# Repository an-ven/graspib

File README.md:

# GrasPiB
GPIB interface board for Raspberry Pi, designed to work with [linux-gpib](https://linux-gpib.sourceforge.io/) gpio bitbang driver. Extra features include: RS232 serial interface, voltage regulator, fan mount and I2C conector.

## Features
* Active GPIB interface circuit using SN7516x bus driver ICs
* RS232 serial interface (MAX3232 level converter), with optionally configurable RTS and CTS lines
* Step down voltage regulator (LM2576) for use with higher voltage power supplies (7-35VDC)
* 25mm cooling fan mounting holes and 2pin JST-PH connector for power
* I2C break out connector with one extra GPIO line (5pin JST-PH connector)
* Stacks on top of a Raspberry Pi

## Configuration options

**JP7 Power supply selection:**

* Close pins 1-2: Power from J5 screw terminal trough onboard regulator circuit (7-35VDC input)
* Close pins 2-3: Power from J5 screw terminal bypassing onboard regulator circuit (5VDC input only !!)
* Leave Open: Power from Raspberry Pi power input USB connector, GrasPiB regulator circuit is isolated

**JP6 Output Voltage select on I2C breakout connector**

* Close pins 1-2: 3,3V on J4 pin 1
* Close pins 2-3: 5V on J4 pin 1

**Enabling RS232 CTS and RTS lines:**

* Close jumpers JP1, JP2, JP4 and JP5, open JP3 positions 1-2 and close positions 2-3
* This change also needs the GPIB DIO3 signal to be reassigned from GPIO16 to GPIO21 (linux-gpib driver code modifications needed)

## Linux-gpib setup instructions

(following instructions were tested on a fresh Raspberry Pi OS Lite image)

0. Setup and configure OS on Raspberry Pi
    * Do as you would with a fresh OS image (passwords, networking, services, communication ports...)

1. Install build tools and dependencies
    * Build tools: `$ sudo apt install build-essential autoconf automake libtool flex bison`
    * RPi kernel headers: `$ sudo apt install raspberrypi-kernel-headers`
    * Python3 headers: `$ sudo apt install python3-dev`

2. Download linux-gpib source files
    * Get release archives (4.3.4 or later) from [https://sourceforge.net/projects/linux-gpib/files](https://sourceforge.net/projects/linux-gpib/files)
    * or get the latest source from [https://sourceforge.net/p/linux-gpib/code/HEAD/tree/](https://sourceforge.net/p/linux-gpib/code/HEAD/tree/)

3. Build and install kernel drivers
    * Enter linux-gpib-kernel directory `$ cd linux-gpib-src-dir/linux-gpib-kernel`
    * Build kernel module by running make `$ make`
    * Install kernel module `$ sudo make install`
    * Update kernel module list `$ sudo depmod -a`
    * Load gpib_bitbang kernel module `$ sudo modprobe gpib_bitbang`
    * Now there should be some `gpib*` devices in `/dev`
    * Make the module loads on boot by adding `gpib_bitbang` line to `/etc/modules-load.d/modules.conf`

**When Raspberry Pi OS kernel gets upgraded, linux-gpib kernel module also needs to be rebuilt and reinstalled.**
Basically just repeat above `make` and `make install` steps when kernel gets upgraded...

4. Build and install user space tools
    * Enter linux-gpib-user directory: `$ cd linux-gpib-src-dir/linux-gpib-user`
    * If building from svn checkout first run bootstrap script: `$ ./bootstrap`
    * Run configure script: `$ ./configure` (run `$ ./configure --help` to list additional options)
    * Build user space tools by running make: `$ make`
    * Install user space tools: `$ sudo make install`
    * Make sure that shared library directory (default: `/usr/local/lib/`) is listed in: `/etc/ld.so.conf.d/`
    * Then run: `$ sudo ldconfig`

5. Configure GPIB interface
    * Open gpib.conf configuration file `$ sudo nano /usr/local/etc/gpib.conf` (default location)
    * Set `board_type = "gpib_bitbang"` and other relevant settings (for details refer to included [`gpib.conf`](extra/gpib.conf) file, [linux-gpib documentetion](https://linux-gpib.sourceforge.io/doc_html/configuration-gpib-conf.html) and included template file `linux-gpib-src-dir/linux-gpib-user/util/template/gpib.conf`)
    * Run gpib_config so the driver reads the configuration file `$ sudo gpib_config --minor 0`
    * Make the last command execute on every startup using crontab entry:
        - Edit crontab for root user: `$ sudo crontab -e`
        - Add line the following line to cron tab file: `@reboot /usr/local/sbin/gpib_config --minor 0`

6. Enable non root users to use GPIB interface without sudo
    - Add new `gpib` system group: `$ sudo groupadd -r gpib`
    - Append your_user_name to `gpib` supplementary group: `$ sudo usermod -a -G gpib your_user_name`
    - Create [`/etc/udev/rules.d/99-gpib.rules`](extra/99-gpib.rules) file and add line: `SUBSYSTEM=="gpib_common", GROUP="gpib", MODE="0660"`
    - Reboot system to apply changes (udevadm utility can also be used, but reboot is dead simple to remember)
    - Test by running `ibtest` without sudo

Above instructions should result in an environment with a functional GPIB interface, C headers and python bindings, ready for use.

## Enabling RS232 Hardware flow control

### Hardware setup:

On the Raspberry Pi CTS and RTS signals are mapped to pins GPIO16 and GPIO17. By default, linux-gpib bitbang driver uses GPIO16 for GPIB DIO3 signal. In order to free up GPIO16, the DIO3 signal can be rewired to GPIO21 by **opening** positions **1-2** (cut traces between pads) and **closing** positions **2-3** on the solder jumper JP3.

By default, CTS and RTS signals are disconnected from the RS232 level converter chip. To connect the CTS and RTS lines, solder jumpers **JP1**, **JP2**, **LP4** and **JP5** need to be **closed**.

Note also, that the extra GPIO17 line on the I2C break out connector J4 can't be used for other purposes when system is configured for RS232 hardware flow control.

### Software setup:

1. Because GPIB signal DIO3 was rewired in hardware to GPIO21, this change needs to reflected in the linux-gpib bitbang driver source code. The source file in question is: `[linux-gpib-sorce-dir]/linux-gpib-kernel/drivers/gpib/gpio/gpib_bitbang.c`, where the signal pairing section needs to be modified as shown below. With the modification done, the linux-gpib driver needs to be compiled as described in step 3 of the "Linux-gpib setup instructions" section of this document.

```
/**********************************************
 *  Signal pairing and pin wiring between the *
 *  Raspberry-Pi connector and the GPIB bus   *
 *                                            *
 *               signal           pin wiring  *
 *            GPIB  Pi-gpio     GPIB  ->  RPi *
**********************************************/
typedef enum {
        D01_pin_nr =  20,     /*   1  ->  38  */
        D02_pin_nr =  26,     /*   2  ->  37  */
//      D03_pin_nr =  16,     /*   3  ->  36  ORIGINAL AND COMMENTED OUT */
        D03_pin_nr =  21,     /*   3  ->  40  MODIFIED TO AVOID CONFLICT WITH CTS SIGNAL */
        D04_pin_nr =  19,     /*   4  ->  35  */
        D05_pin_nr =  13,     /*  13  ->  33  */
        D06_pin_nr =  12,     /*  14  ->  32  */
        D07_pin_nr =   6,     /*  15  ->  31  */
        D08_pin_nr =   5,     /*  16  ->  29  */
        EOI_pin_nr =   9,     /*   5  ->  21  */
        DAV_pin_nr =  10,     /*   6  ->  19  */
        NRFD_pin_nr = 24,     /*   7  ->  18  */
        NDAC_pin_nr = 23,     /*   8  ->  16  */
        IFC_pin_nr =  22,     /*   9  ->  15  */
        SRQ_pin_nr =  11,     /*  10  ->  23  */
        _ATN_pin_nr = 25,     /*  11  ->  22  */
        REN_pin_nr =  27,     /*  17  ->  13  */
...

```

2. Next the [`uart-ctsrts.dtbo`](extra/uart-ctsrts.dtbo) file (included in extra directory) needs to be copied in to the `/boot/overlays` directory and add the following lines need to be added to the `/boot/config.txt` file:

```
enable_uart=1
dtoverlay=disable-bt
dtoverlay=uart-ctsrts
```

3. Reboot the system to apply changes.

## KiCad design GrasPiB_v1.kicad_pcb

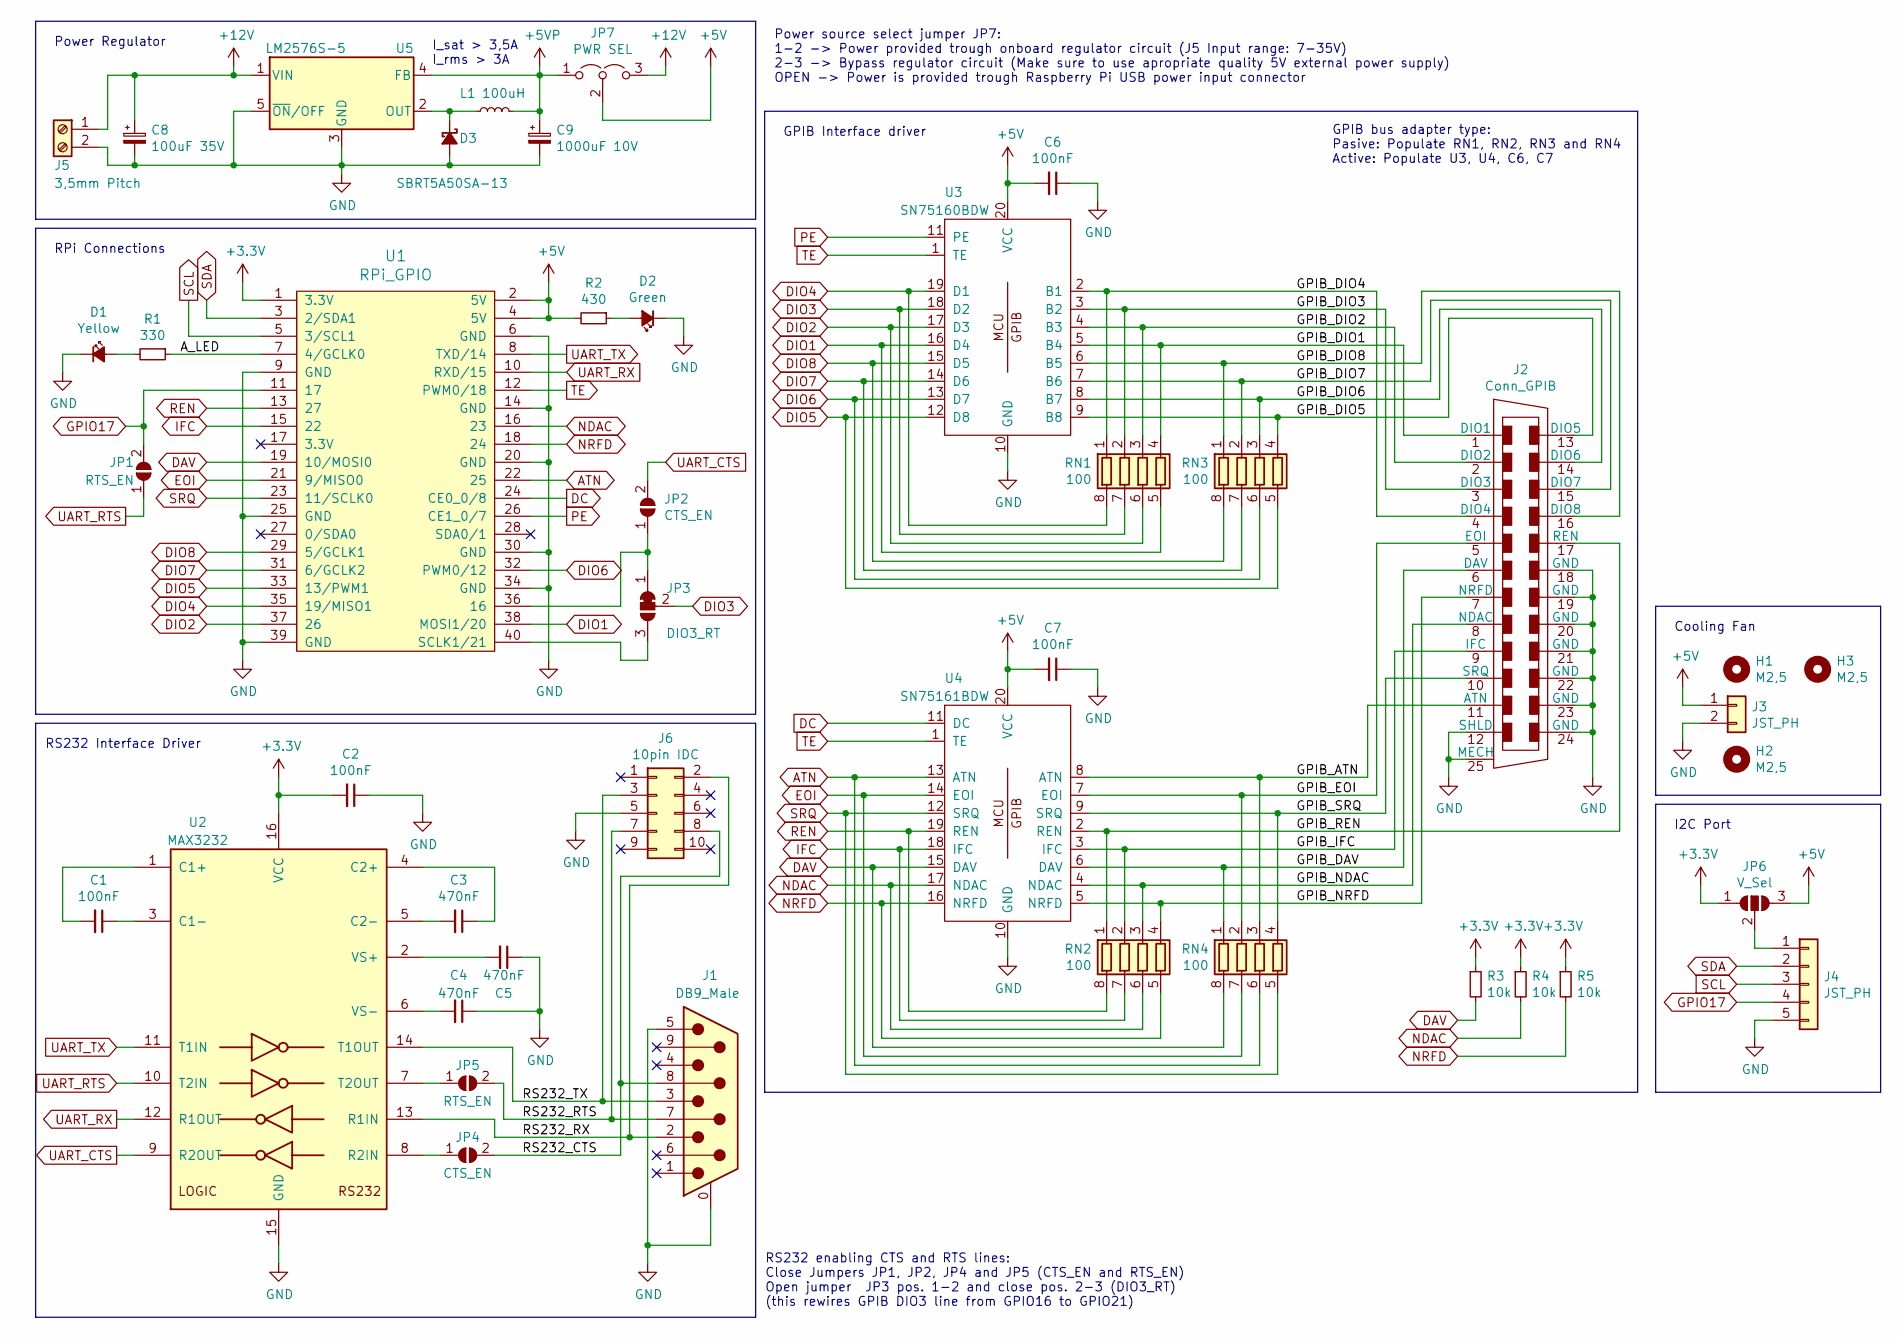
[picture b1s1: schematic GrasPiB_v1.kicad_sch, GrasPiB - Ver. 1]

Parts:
C1, C2, C6, C7: 100nF; C_0603_1608Metric_Pad1.08x0.95mm_HandSolder
C3, C4, C5: 470nF; C_0603_1608Metric_Pad1.08x0.95mm_HandSolder
C8: 100uF 35V; CP_Elec_10x10
C9: 1000uF 10V; CP_Elec_10x10
D1: Yellow; LED_0603_1608Metric_Pad1.05x0.95mm_HandSolder
D2: Green; LED_0603_1608Metric_Pad1.05x0.95mm_HandSolder
D3: SBRT5A50SA-13; D_SMA_Handsoldering
H1, H2, H3: M2,5; MountingHole_2.7mm_M2.5
J1: DB9_Male; DSUB-9_Male_Horizontal_P2.77x2.84mm_EdgePinOffset7.70mm_Hou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
J2: Conn_GPIB; NorComp_112-024-213R001
J3: JST_PH; JST_PH_B2B-PH-K_1x02_P2.00mm_Vertical
J4: JST_PH; JST_PH_B5B-PH-K_1x05_P2.00mm_Vertical
J5: 3,5mm Pitch; TerminalBlock_Phoenix_PT-1,5-2-3.5-H_1x02_P3.50mm_Horizontal
J6: 10pin IDC; IDC-Header_2x05_P2.54mm_Vertical
JP1, JP5: RTS_EN; SolderJumper-2_P1.3mm_Open_RoundedPad1.0x1.5mm
JP2, JP4: CTS_EN; SolderJumper-2_P1.3mm_Open_RoundedPad1.0x1.5mm
JP3: DIO3_RT; SolderJumper-3_P1.3mm_Bridged12_RoundedPad1.0x1.5mm
JP6: V_Sel; SolderJumper-3_P1.3mm_Open_RoundedPad1.0x1.5mm
JP7: PWR SEL; PinHeader_1x03_P2.54mm_Vertical
L1: 100uH; L_Wuerth_WE-PD-Typ-LS
R1: 330; R_0603_1608Metric_Pad0.98x0.95mm_HandSolder
R2: 430; R_0603_1608Metric_Pad0.98x0.95mm_HandSolder
R3, R4, R5: 10k; R_0603_1608Metric_Pad0.98x0.95mm_HandSolder
RN1, RN2, RN3, RN4: 100; R_Array_Convex_4x1206
U1: RPi_GPIO; RPi4_Hat
U2: MAX3232; SO-16_3.9x9.9mm_P1.27mm
U3: SN75160BDW; SO-20_12.8x7.5mm_P1.27mm
U4: SN75161BDW; SO-20_12.8x7.5mm_P1.27mm
U5: LM2576S-5; TO-263-5_TabPin3

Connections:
+3V3: C2.2, JP6.1 (A), R3.1, R4.1, R5.1, U1.1 (3.3V), U2.16 (VCC)
+5V: C6.2, C7.2, J3.1, JP6.3 (B), JP7.2 (C), R2.2, U1.2 (5V), U1.4 (5V), U3.20 (VCC), U4.20 (VCC)
+5VP: C9.1, JP7.1 (A), L1.2, U5.4 (FB)
+12V: C8.1, J5.1, JP7.3 (B), U5.1 (VIN)
/A_LED: R1.1, U1.7 (4/GCLK0)
/GPIB_ATN: J2.11 (ATN), RN4.3 (R3.1), U4.8 (ATN)
/GPIB_DAV: J2.6 (DAV), RN4.1 (R1.1), U4.6 (DAV)
/GPIB_DIO1: J2.1 (DIO1), RN1.4 (R4.1), U3.5 (B4)
/GPIB_DIO2: J2.2 (DIO2), RN1.3 (R3.1), U3.4 (B3)
/GPIB_DIO3: J2.3 (DIO3), RN1.2 (R2.1), U3.3 (B2)
/GPIB_DIO4: J2.4 (DIO4), RN1.1 (R1.1), U3.2 (B1)
/GPIB_DIO5: J2.13 (DIO5), RN3.4 (R4.1), U3.9 (B8)
/GPIB_DIO6: J2.14 (DIO6), RN3.3 (R3.1), U3.8 (B7)
/GPIB_DIO7: J2.15 (DIO7), RN3.2 (R2.1), U3.7 (B6)
/GPIB_DIO8: J2.16 (DIO8), RN3.1 (R1.1), U3.6 (B5)
/GPIB_EOI: J2.5 (EOI), RN4.2 (R2.1), U4.7 (EOI)
/GPIB_IFC: J2.9 (IFC), RN2.2 (R2.1), U4.3 (IFC)
/GPIB_NDAC: J2.8 (NDAC), RN2.3 (R3.1), U4.4 (NDAC)
/GPIB_NRFD: J2.7 (NRFD), RN2.4 (R4.1), U4.5 (NRFD)
/GPIB_REN: J2.17 (REN), RN2.1 (R1.1), U4.2 (REN)
/GPIB_SRQ: J2.10 (SRQ), RN4.4 (R4.1), U4.9 (SRQ)
/RS232_CTS: J1.8, J6.8, JP4.2 (B)
/RS232_RTS: J1.7, J6.7, JP5.2 (B)
/RS232_RX: J1.2, J6.2, U2.13 (R1IN)
/RS232_TX: J1.3, J6.3, U2.14 (T1OUT)
ATN: RN4.6 (R3.2), U1.22 (25), U4.13 (ATN)
DAV: R3.2, RN4.8 (R1.2), U1.19 (10/MOSI0), U4.15 (DAV)
DC: U1.24 (CE0_0/8), U4.11 (DC)
DIO1: RN1.5 (R4.2), U1.38 (MOSI1/20), U3.16 (D4)
DIO2: RN1.6 (R3.2), U1.37 (26), U3.17 (D3)
DIO3: JP3.2 (C), RN1.7 (R2.2), U3.18 (D2)
DIO4: RN1.8 (R1.2), U1.35 (19/MISO1), U3.19 (D1)
DIO5: RN3.5 (R4.2), U1.33 (13/PWM1), U3.12 (D8)
DIO6: RN3.6 (R3.2), U1.32 (PWM0/12), U3.13 (D7)
DIO7: RN3.7 (R2.2), U1.31 (6/GCLK2), U3.14 (D6)
DIO8: RN3.8 (R1.2), U1.29 (5/GCLK1), U3.15 (D5)
EOI: RN4.7 (R2.2), U1.21 (9/MISO0), U4.14 (EOI)
GND: C2.1, C4.1, C5.1, C6.1, C7.1, C8.2, C9.2, D1.1 (K), D2.1 (K), D3.2 (A), J1.0 (PAD), J1.5, J2.12 (SHLD), J2.18 (GND), J2.19 (GND), J2.20 (GND), J2.21 (GND), J2.22 (GND), J2.23 (GND), J2.24 (GND), J2.25 (MECH), J3.2, J4.5, J5.2, J6.5, U1.6 (GND), U1.9 (GND), U1.14 (GND), U1.20 (GND), U1.25 (GND), U1.30 (GND), U1.34 (GND), U1.39 (GND), U2.15 (GND), U3.10 (GND), U4.10 (GND), U5.3 (GND), U5.5 (~ON/OFF)
GPIO17: J4.4, JP1.2 (B), U1.11 (17)
IFC: RN2.7 (R2.2), U1.15 (22), U4.18 (IFC)
NDAC: R4.2, RN2.6 (R3.2), U1.16 (23), U4.17 (NDAC)
NRFD: R5.2, RN2.5 (R4.2), U1.18 (24), U4.16 (NRFD)
unnamed: C1.1, U2.3 (C1-)
unnamed: C1.2, U2.1 (C1+)
unnamed: C3.1, U2.4 (C2+)
unnamed: C3.2, U2.5 (C2-)
unnamed: C4.2, U2.6 (VS-)
unnamed: C5.2, U2.2 (VS+)
unnamed: D1.2 (A), R1.2
unnamed: D2.2 (A), R2.1
unnamed: D3.1 (K), L1.1, U5.2 (OUT)
unnamed: J4.1, JP6.2 (C)
unnamed: JP2.1 (A), JP3.1 (A), U1.36 (16)
unnamed: JP3.3 (B), U1.40 (SCLK1/21)
unnamed: JP4.1 (A), U2.8 (R2IN)
unnamed: JP5.1 (A), U2.7 (T2OUT)
PE: U1.26 (CE1_0/7), U3.11 (PE)
REN: RN2.8 (R1.2), U1.13 (27), U4.19 (REN)
SCL: J4.3, U1.5 (3/SCL1)
SDA: J4.2, U1.3 (2/SDA1)
SRQ: RN4.5 (R4.2), U1.23 (11/SCLK0), U4.12 (SRQ)
TE: U1.12 (PWM0/18), U3.1 (TE), U4.1 (TE)
UART_CTS: JP2.2 (B), U2.9 (R2OUT)
UART_RTS: JP1.1 (A), U2.10 (T2IN)
UART_RX: U1.10 (RXD/15), U2.12 (R1OUT)
UART_TX: U1.8 (TXD/14), U2.11 (T1IN)

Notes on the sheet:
Power Regulator
I2C Port
Power source select jumper JP7: 1-2 -> Power provided trough onboard regulator circuit (J5 Input range: 7-35V) 2-3 -> Bypass regulator circuit (Make sure to use apropriate quality 5V external power supply) OPEN -> Power is provided trough Raspberry Pi USB power input connector
GPIB bus adapter type: Pasive: Populate RN1, RN2, RN3 and RN4 Active: Populate U3, U4, C6, C7
GPIB Interface driver
I_sat > 3,5A I_rms > 3A
RS232 enabling CTS and RTS lines: Close Jumpers JP1, JP2, JP4 and JP5 (CTS_EN and RTS_EN) Open jumper JP3 pos. 1-2 and close pos. 2-3 (DIO3_RT) (this rewires GPIB DIO3 line from GPIO16 to GPIO21)
RS232 Interface Driver
RPi Connections
Cooling Fan

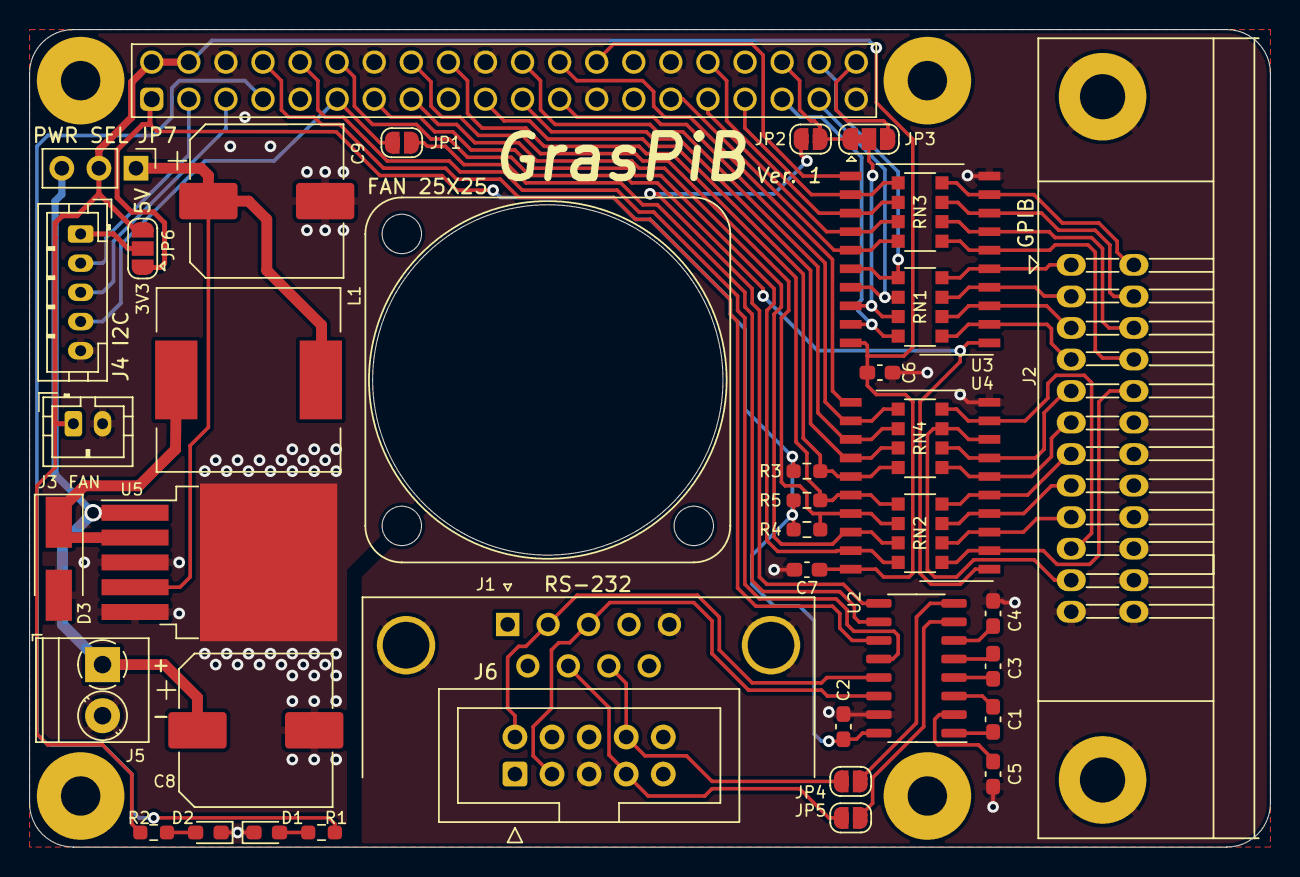
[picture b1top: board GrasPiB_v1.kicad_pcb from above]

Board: 2 copper layers, 85.0 x 56.0 mm, 43 parts (0 on the bottom side), 66 nets.

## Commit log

2021-12-30 Add initial design files and documentation
2021-12-30 Update README, add photo
2021-12-30 Add image in README.md
2022-01-02 Add gpib.conf file and link to it in README
2022-01-13 Rewire RTS and CTS signals the correct way
2022-01-13 Update gerber files
2022-03-12 Convert design files to KiCAD 6
2022-03-12 Add arduino adapter board design files
2022-03-13 Extend documentation
2022-03-13 Add some links to README.md
